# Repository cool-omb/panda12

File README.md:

# panda12

## 概要 Overview

Bluetooth 接続の 12 キーキーボード。

キーマップの変更等がWiFi経由で出来る。

## 使い方 Usage
### キーボード使用時
スライドスイッチで電源を入れ、 `Test_keyboard` にBluetooth接続する。
### キーマップ設定時
設定ボタンを押しながら電源を入れ、 `Preference_keyboard` にWiFi接続する。
ブラウザからキーマップを変更後、 `保存` ボタンをクリックすることで変更が反映される。

※ 有線LANを接続しているデバイスからは、キーマップ変更ページへ自動で遷移しないことがあるので、 `192.168.4.1` へ手動でアクセスしてください。

## 必要要件 Requirement

- KiCad 6.0.10

  - [Kailh socket MX footprint](https://github.com/daprice/keyswitches.pretty)

- [Arduino IDE 2.0.3](https://www.arduino.cc/en/software)
  - [Arduino core for the ESP32 v2.0.4](https://github.com/espressif/arduino-esp32#installation-instructions)
  - [NimBLE-Arduino v1.4.0](https://github.com/h2zero/NimBLE-Arduino)
  - [ESP32-NimBLE-Keyboard v1.4.0](https://github.com/wakwak-koba/ESP32-NimBLE-Keyboard)
  - [arduino-esp8266fs-plugin v0.5.0](https://github.com/esp8266/arduino-esp8266fs-plugin)
  - [Arduino ESP32 filesystem uploader v1.0](https://github.com/me-no-dev/arduino-esp32fs-plugin)
  - [ESP8266_Spiram](https://github.com/Gianbacchio/ESP8266_Spiram)
  - [ESPAsyncWebServer](https://github.com/me-no-dev/ESPAsyncWebServer)
  - [ArduinoJson](https://github.com/bblanchon/ArduinoJson)

## 注意事項 Note
- BLE通信の安定性は上記のライブラリに依存しており、通信するデバイスによっては動作が不安定になることもございます。
- `Blekeyboard.print()` の挙動が不安定で、これを利用しているテキスト出力もまた安定的に動作しません。

## 参考 Reference

- [CaptivePortalExample](https://github.com/elliotmade/ESP32-Captive-Portal-Example/blob/test/src/main.cpp)

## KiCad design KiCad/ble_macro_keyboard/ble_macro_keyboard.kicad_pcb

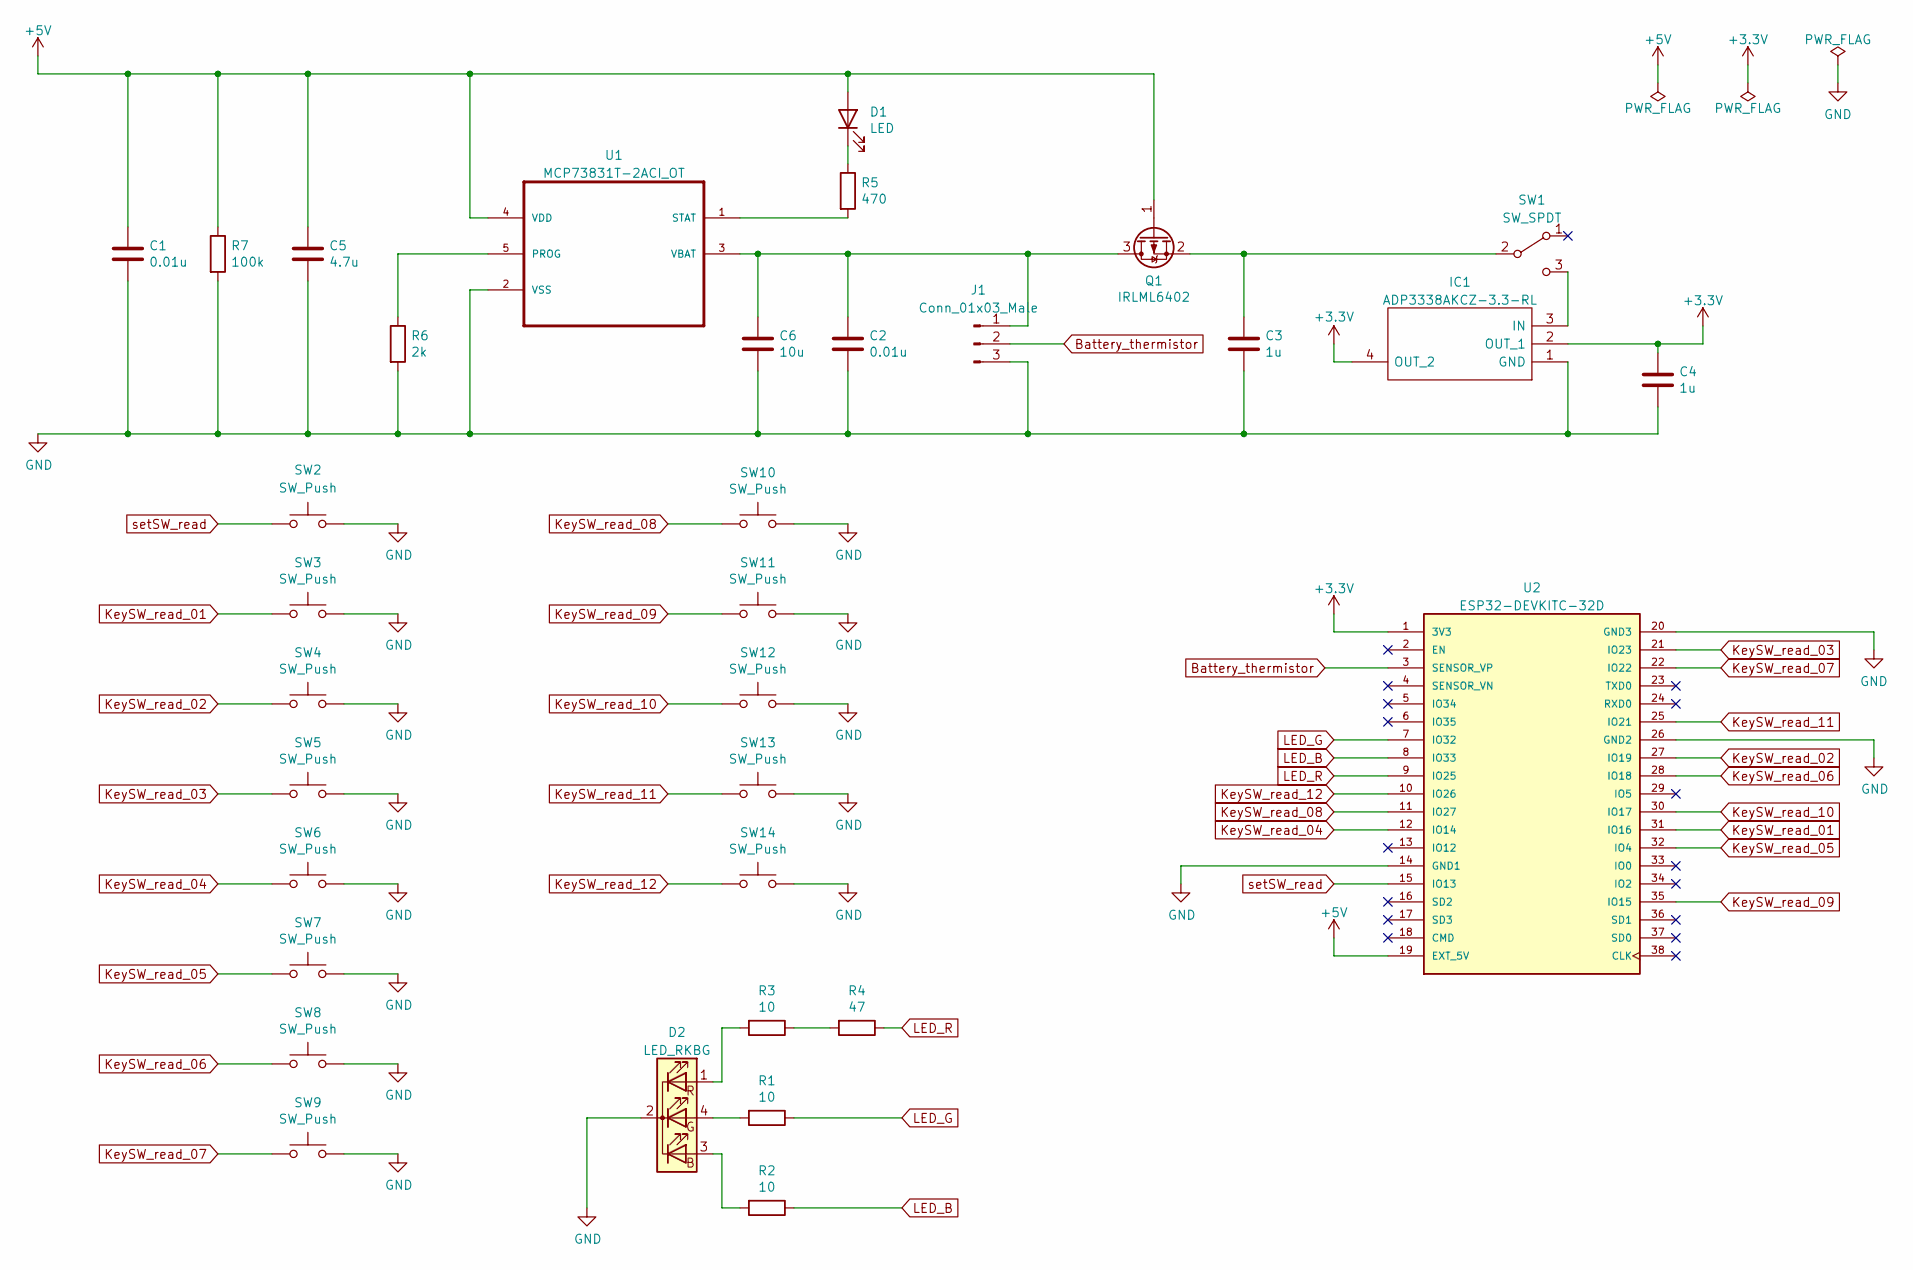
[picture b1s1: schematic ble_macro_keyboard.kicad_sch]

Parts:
C1, C2: 0.01u; C_0603_1608Metric_Pad1.08x0.95mm_HandSolder
C3, C4: 1u; C_0603_1608Metric_Pad1.08x0.95mm_HandSolder
C5: 4.7u; CP_Radial_D5.0mm_P2.00mm
C6: 10u; CP_Radial_D5.0mm_P2.00mm
D1: LED; LED_D3.0mm
D2: LED_RKBG; LED_D5.0mm-4_RGB
IC1: ADP3338AKCZ-3.3-RL; SOT230P700X180-4N; Mouser Part Number 584-ADP3338AKCZ3.3R
J1: Conn_01x03_Male; JST_SHL_SM03B-SHLS-TF_1x03-1MP_P1.00mm_Horizontal
Q1: IRLML6402; SOT-23
R1, R2, R3: 10; R_0603_1608Metric_Pad1.05x0.95mm_HandSolder
R4: 47; R_0603_1608Metric_Pad1.05x0.95mm_HandSolder
R5: 470; R_0603_1608Metric_Pad1.05x0.95mm_HandSolder
R6: 2k; R_0603_1608Metric_Pad1.05x0.95mm_HandSolder
R7: 100k; R_0603_1608Metric_Pad1.05x0.95mm_HandSolder
SW1: SW_SPDT; SW_Slide_SPDT_MSK-12C02
SW2: SW_Push; SW_Push_Dual_x2_TS-4401
SW3, SW4, SW5, SW6, SW7, SW8, SW9, SW10, SW11, SW12, SW13, SW14: SW_Push; Kailh_socket_MX
U1: MCP73831T-2ACI_OT; SOT95P280X145-5N
U2: ESP32-DEVKITC-32D; MODULE_ESP32-DEVKITC-32D; PARTREV 4

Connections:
+3.3V: C4.1, IC1.2 (OUT_1), IC1.4 (OUT_2), U2.1 (3V3)
+5V: C1.1, C5.1, D1.2 (A), Q1.1 (G), R7.1, U1.4 (VDD), U2.19 (EXT_5V)
Battery_thermistor: J1.2, U2.3 (SENSOR_VP)
GND: C1.2, C2.2, C3.2, C4.2, C5.2, C6.2, D2.2 (K), IC1.1 (GND), J1.3, R6.2, R7.2, SW2.2, SW3.2, SW4.2, SW5.2, SW6.2, SW7.2, SW8.2, SW9.2, SW10.2, SW11.2, SW12.2, SW13.2, SW14.2, U1.2 (VSS), U2.14 (GND1), U2.20 (GND3), U2.26 (GND2)
KeySW_read_01: SW3.1, U2.31 (IO16)
KeySW_read_02: SW4.1, U2.27 (IO19)
KeySW_read_03: SW5.1, U2.21 (IO23)
KeySW_read_04: SW6.1, U2.12 (IO14)
KeySW_read_05: SW7.1, U2.32 (IO4)
KeySW_read_06: SW8.1, U2.28 (IO18)
KeySW_read_07: SW9.1, U2.22 (IO22)
KeySW_read_08: SW10.1, U2.11 (IO27)
KeySW_read_09: SW11.1, U2.35 (IO15)
KeySW_read_10: SW12.1, U2.30 (IO17)
KeySW_read_11: SW13.1, U2.25 (IO21)
KeySW_read_12: SW14.1, U2.10 (IO26)
LED_B: R2.1, U2.8 (IO33)
LED_G: R1.1, U2.7 (IO32)
LED_R: R4.1, U2.9 (IO25)
unnamed: C2.1, C6.1, J1.1, Q1.3 (D), U1.3 (VBAT)
unnamed: C3.1, Q1.2 (S), SW1.2 (B)
unnamed: D1.1 (K), R5.1
unnamed: D2.1 (RA), R3.2
unnamed: D2.3 (BA), R2.2
unnamed: D2.4 (GA), R1.2
unnamed: IC1.3 (IN), SW1.3 (C)
unnamed: R3.1, R4.2
unnamed: R5.2, U1.1 (STAT)
unnamed: R6.1, U1.5 (PROG)
setSW_read: SW2.1, U2.15 (IO13)

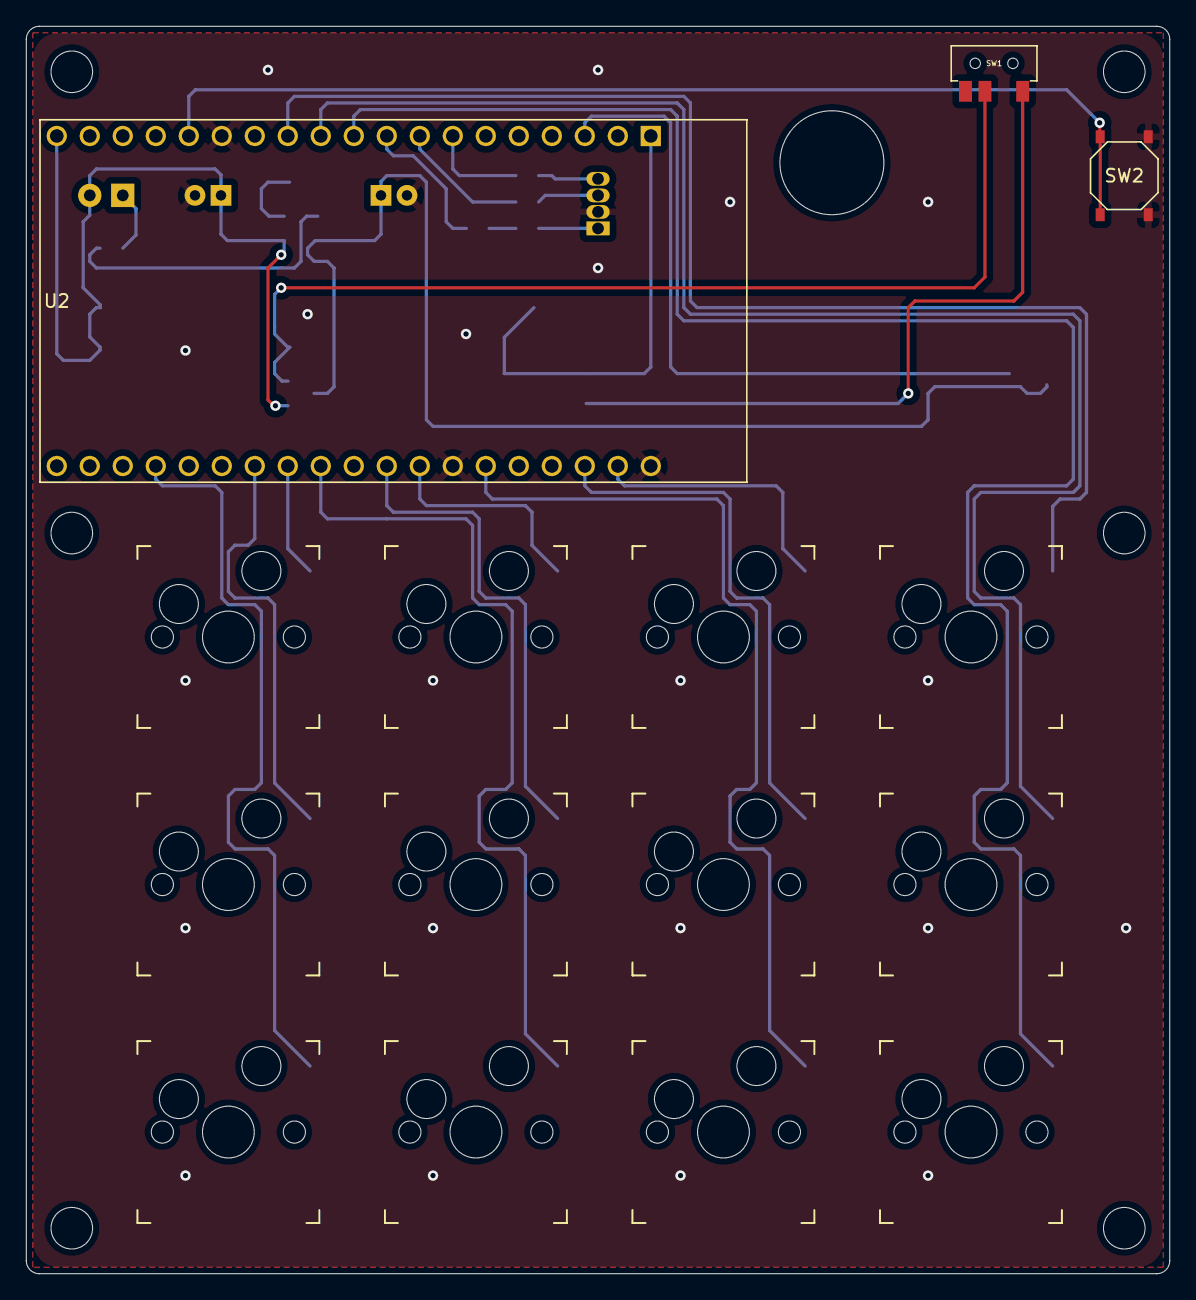
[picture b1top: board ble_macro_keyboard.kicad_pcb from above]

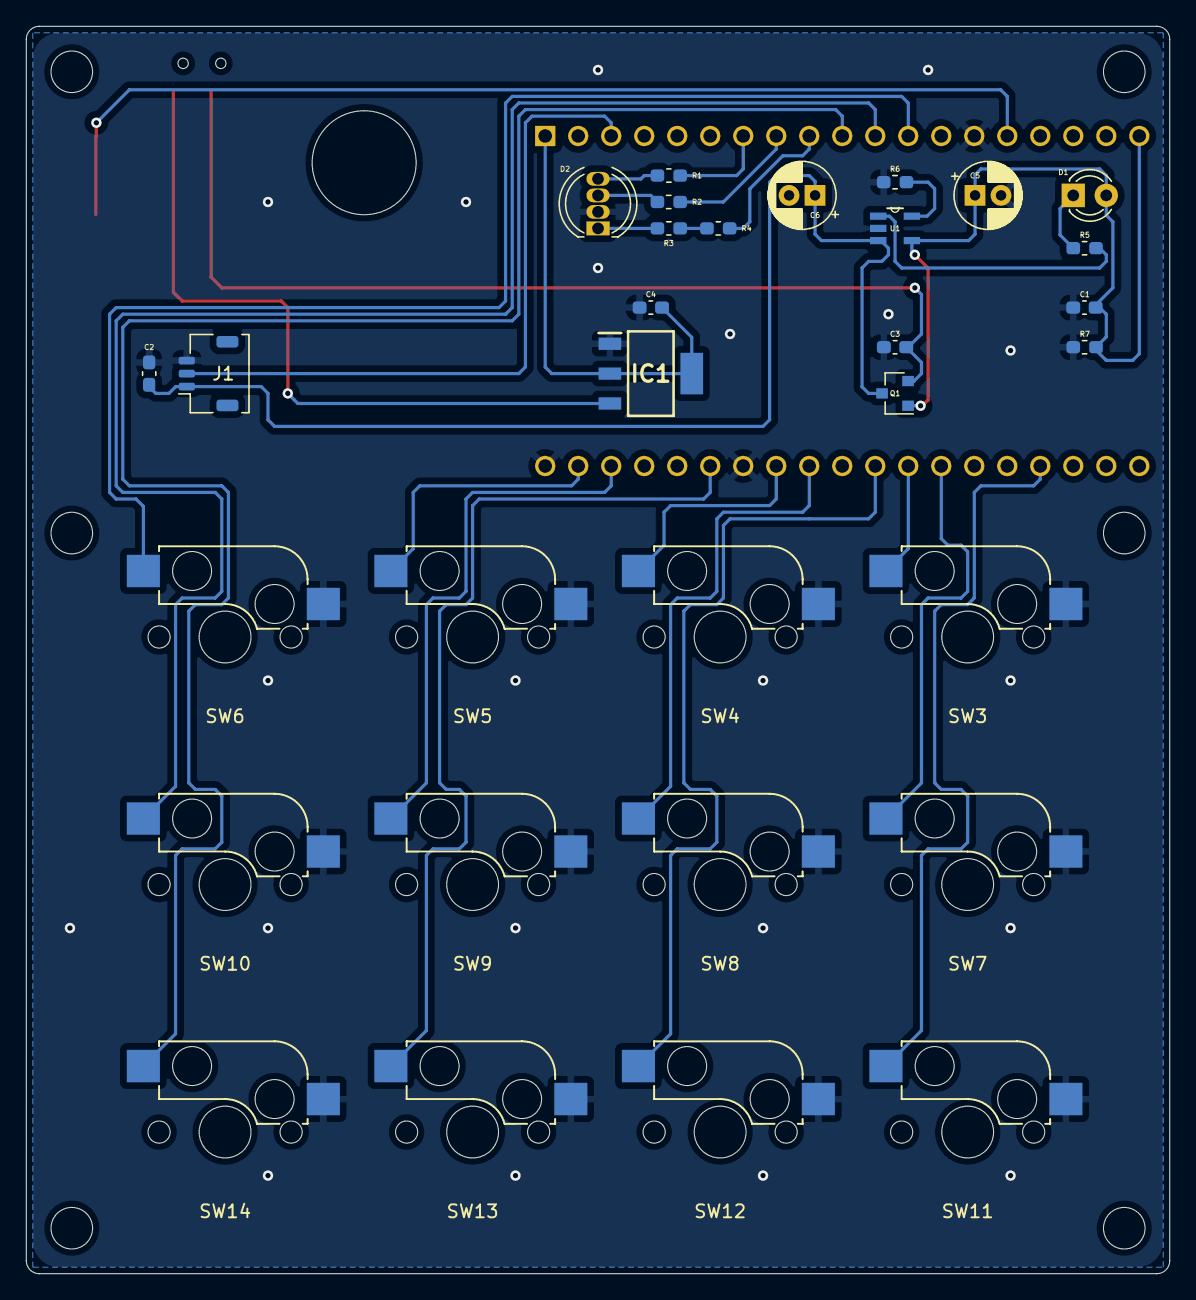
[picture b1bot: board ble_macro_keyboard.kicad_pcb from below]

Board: 2 copper layers, 88.0 x 96.0 mm, 34 parts (19 on the bottom side), 30 nets.

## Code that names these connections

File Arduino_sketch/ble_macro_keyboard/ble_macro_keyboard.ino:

#include <Arduino.h>
#include <AsyncTCP.h>
#include "ESPAsyncWebServer.h"
#include "DNSServer.h"
#include <SPIFFS.h>
#include "ArduinoJson.h"
#include <FS.h>
#include <BleKeyboard.h>

using namespace std;

#define LED_R_PIN 25
#define LED_G_PIN 32
#define LED_B_PIN 33
#define LEDC_BASE_FREQ 12800
#define LEDC_RESOLUTION 8
#define LEDC_CHANNEL_R 0
#define LEDC_CHANNEL_G 1
#define LEDC_CHANNEL_B 2

#define PREFERENCE_SW_PIN 13
#define DEFAULT_DEVICE_NAME "Test_Keyboard"
#define DEFAULT_DEVICE_MANUFACTURER "Panda12_manufacturer"

bool isConfig = false;
const vector<int> SW_PINS{16, 19, 23, 14, 4, 18, 22, 27, 15, 17, 21, 26};

const char *SSID = "Preference_Keyboard";

int LAYER_LENGTH = -1;
int OUTPUT_LENGTH = -1;
int INPUT_LENGTH = -1;
int INTERVAL_MS = 100;
int IS_LED_ON = 0;
int LED_R_BRIGHTNESS = 0;
int LED_G_BRIGHTNESS = 0;
int LED_B_BRIGHTNESS = 0;

AsyncWebServer server(80);
DNSServer dnsServer;

BleKeyboard bleKeyboard(DEFAULT_DEVICE_NAME, DEFAULT_DEVICE_MANUFACTURER, 100);
DynamicJsonDocument preferenceDocument(65536);

void handleUpload(AsyncWebServerRequest *request, String filename, size_t index, uint8_t *data, size_t len, bool final)
{
  return 1;
}

void handleBody(AsyncWebServerRequest *request, uint8_t *data, size_t len, size_t index, size_t total)
{
  if (!index)
  {
    request->_tempFile = SPIFFS.open("/keymap.json", "w");
  }
  request->_tempFile.write(data, len);
  if (index + len == total)
  {
    request->_tempFile.close();
    request->send(200, "text/plain", "Write keymap.json success.");
  }
}

void webServerSetup()
{
  server.serveStatic("/", SPIFFS, "/").setDefaultFile("index.html");
  server.on(
      "/post",
      HTTP_POST,
      [](AsyncWebServerRequest *request)
      {
        request->send(200, "text/plain", "keymap.json posted.");
      },
      handleUpload,
      handleBody);

  server.onNotFound([](AsyncWebServerRequest *request)
                    {
    String redirectUrl = "http://";
    redirectUrl += WiFi.softAPIP().toString();
    redirectUrl += "/";
    request->redirect(redirectUrl); });

  server.begin();
}

void setupLed()
{
  if (IS_LED_ON)
  {
    ledcSetup(LEDC_CHANNEL_R, LEDC_BASE_FREQ, LEDC_RESOLUTION);
    ledcAttachPin(LED_R_PIN, LEDC_CHANNEL_R);
    ledcWrite(LEDC_CHANNEL_R, LED_R_BRIGHTNESS);
    ledcSetup(LEDC_CHANNEL_G, LEDC_BASE_FREQ, LEDC_RESOLUTION);
    ledcAttachPin(LED_G_PIN, LEDC_CHANNEL_G);
    ledcWrite(LEDC_CHANNEL_G, LED_G_BRIGHTNESS);
    ledcSetup(LEDC_CHANNEL_B, LEDC_BASE_FREQ, LEDC_RESOLUTION);
    ledcAttachPin(LED_B_PIN, LEDC_CHANNEL_B);
    ledcWrite(LEDC_CHANNEL_B, LED_B_BRIGHTNESS);
  }
}

void setupPinMode()
{
  pinMode(PREFERENCE_SW_PIN, INPUT_PULLUP);
  for (int pin : SW_PINS)
  {
    pinMode(pin, INPUT_PULLUP);
  }
}

void setupPreferenceMode()
{
  WiFi.softAP(SSID);
  dnsServer.start(53, "*", WiFi.softAPIP());
  webServerSetup();
}

void setupKeyboardMode()
{
  File file = SPIFFS.open("/keymap.json", "r");
  DeserializationError error = deserializeJson(preferenceDocument, file);
  if (error)
  {
    return 0;
  }
  JsonObject root = preferenceDocument.as<JsonObject>();

  file.close();

  LAYER_LENGTH = preferenceDocument["length"]["layer"].as<int>();
  OUTPUT_LENGTH = preferenceDocument["length"]["output"].as<int>();
  INPUT_LENGTH = preferenceDocument["length"]["input"].as<int>();
  INTERVAL_MS = preferenceDocument["preference"]["interval"].as<int>();
  IS_LED_ON = preferenceDocument["preference"]["ledOn"].as<int>();
  LED_R_BRIGHTNESS = preferenceDocument["preference"]["ledRed"].as<int>();
  LED_G_BRIGHTNESS = preferenceDocument["preference"]["ledGreen"].as<int>();
  LED_B_BRIGHTNESS = preferenceDocument["preference"]["ledBlue"].as<int>();

  setupLed();

  delay(20);
  bleKeyboard.begin();
  delay(100);
}

unsigned int readAllPushedBit()
{
  unsigned int pushed = 0;
  for (int i = 0; i < (int)SW_PINS.size(); ++i)
  {
    if (digitalRead(SW_PINS[i]) == LOW)
    {
      pushed |= (1 << i);
    }
  }
  return pushed;
}

int getKeyNumber(int layerIndex, int outputIndex, int inputIndex)
{
  return preferenceDocument["assign"][layerIndex][outputIndex][inputIndex]["num"].as<int>();
}

String getKeyText(int layerIndex, int outputIndex, int inputIndex)
{
  return preferenceDocument["assign"][layerIndex][outputIndex][inputIndex]["text"].as<String>();
}

void loopKeyboard()
{
  // static variable defind.
  static unsigned int swPushedBit = 0;
  static int layerIndex = 0;

  // measures for chattering.
  if (swPushedBit != readAllPushedBit())
  {
    delay(10);
    if (bleKeyboard.isConnected())
    {
      unsigned int currentSwPushedBit = readAllPushedBit();
      unsigned int xorSwPushedBit = currentSwPushedBit ^ swPushedBit;

      int currentLayerIndex = 0;
      for (int i = 0; i < INPUT_LENGTH; ++i)
      {
        if (currentSwPushedBit & (1 << i))
        {
          if (getKeyNumber(0, 0, i) >= 256)
          {
            currentLayerIndex += getKeyNumber(0, 0, i) - 256;
          }
        }
      }
      if (layerIndex != currentLayerIndex)
      {
        bleKeyboard.releaseAll();
        for (int i = 0; i < INPUT_LENGTH; ++i)
        {
          if (currentSwPushedBit & (1 << i))
          {
            int keyNumber = getKeyNumber(currentLayerIndex, 0, i);
            if (keyNumber < 0)
            {
              bleKeyboard.print(getKeyText(currentLayerIndex, 0, i));
            }
            else if (keyNumber < 256)
            {
              bleKeyboard.press(keyNumber);
            }
          }
        }
        layerIndex = currentLayerIndex;
      }
      else
      {
        for (int i = 0; i < (int)SW_PINS.size(); ++i)
        {
          if (xorSwPushedBit & (1 << i))
          {
            int keyNumber = getKeyNumber(currentLayerIndex, 0, i);
            if (currentSwPushedBit & (1 << i))
            {
              if (keyNumber < 0)
              {
                bleKeyboard.print(getKeyText(currentLayerIndex, 0, i));
              }
              else if (keyNumber < 256)
              {
                bleKeyboard.press(keyNumber);
              }
            }
            else
            {
              if (0 <= keyNumber && keyNumber < 256)
              {
                bleKeyboard.release(keyNumber);
              }
            }
          }
        }
      }
      swPushedBit = currentSwPushedBit;
    }
  }
  delay(INTERVAL_MS);
}

void setup()
{
  setupLed();

  SPIFFS.begin();

  setupPinMode();
  if (digitalRead(PREFERENCE_SW_PIN) == LOW)
  {
    isConfig = true;
    setupPreferenceMode();
  }
  else
  {
    setupKeyboardMode();
  }
}

void loop()
{
  if (isConfig)
  {
    dnsServer.processNextRequest();
  }
  else
  {
    loopKeyboard();
  }
}

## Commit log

2021-06-18 add requirement
2021-06-18 add requirement fixed.
2022-06-14 プレゼン向けキー配置
2022-07-10 replace KiCADv6 and new version circuit diagram.
2022-07-10 library replace and connect symbol to footprint.
2022-07-11 add keyswitches.pretty
2022-07-12 keyswitch add to 12.
2022-07-22 ライブラリを相対パスへ変更
2022-07-22 コネクタを除き、シンボルとフットプリントの紐づけ完了
2022-07-22 JST SHコネクタ 3pin のフットプリント作成
2022-07-22 git submodule削除
2022-07-24 基板図配線のためにマイコンのピン入れ替え
2022-07-24 リファレンス指定子を昇順に変更
2022-07-24 シルクスクリーンのリファレンス指定子の印字位置を内側に変更
2022-07-24 [fix] Vsysラベルを3.3vへ修正
2022-07-25 [update] GND以外パターン接続
2022-07-25 [add] ライブラリ及び回路図にNPTH_8mmを追加
2022-07-25 [fix] Ble_keyboardフットプリントライブラリのSWがGNDに接続するように解決
2022-07-25 [fix] Ble_keyboardライブラリのシルクスクリーンとパッドが干渉するライブラリを修正
2022-07-25 [add] 底板の図面出力
2022-07-25 [add] キースイッチプレートの図面出力
2022-07-25 [fix] ハンダマスクの最小幅を0に設定
2022-07-25 [fix] キースイッチプレートの角をフィレット
2022-07-25 [fix] 底板および基板外形の角をフィレット
2022-07-25 [add] 基盤製造用ファイルの出力
2022-07-25 [fix] Elecrow発注用にgerberファイル名変更
2022-07-25 [fix] User.drawingsレイヤーに底板のアクリルプレート、User.Eco1にキースイッチプレートのアクリルの図面を設定
2022-08-02 ignore KiCAD backups
2022-08-02 KiCAD cache file ignore
2022-08-02 [fix] KiCADのキャッシュを除外
2022-08-05 change NimBLE lib.
2022-08-06 [update] 12鍵マクロキーのピン配置に対応
2022-08-08 [fix] ピン配置の宣言をvectorに変更
2022-08-09 [update] EEPROM 読み書きの検証
2022-08-10 [refactor] 変数名の整理
2022-08-10 [refactor] SETTING_SW を keymaps から分離
2022-08-10 [add] キーマップのレイヤー追加
2022-08-10 [fix] vscode exclude
2022-08-10 [fix] Builtin LED delete.
2022-08-10 [add] wifi access point test
2022-08-10 [add] static ip
2022-08-10 [update] device value load rom
2022-08-10 [add] dynamic html create test.
2022-08-10 [add] EEPROM write from HTML.
2022-08-10 [refactor] vector to int array.
2022-08-11 [add] delay_time
2022-08-11 if to switch
2022-08-11 [add] text inputs
2022-08-13 [add] led config add.
2022-08-13 [doc] Readme 必要要件更新
2022-12-26 [add] Pull ISLT65 repo
    Arduino sketch for wifi key preference.
2022-12-27 [add] Add onclick on keysw
    When click key sw, this value put form.
2022-12-27 [add] Change keymap value
    When input and change form value, set changed value to keymap object.
2022-12-27 [update] ESPAsyncWebServer included
    Changed Async from webserver.
2022-12-29 [add] Write json esp32 flash
    POST body to SPIFFS write.
2022-12-29 [add] Preference mode added.
    When push preference sw, Keymap preference mode.
2022-12-29 [add] Read keymap.json
    Load json and get value.
2022-12-29 [add] version1.2
2022-12-29 [update] Added requirement and usage
    Update requirement, usage and note.
2022-12-31 [fix] Changed SSID
    Because SSID is not correct, so it's fixed.
2024-01-03 [doc] Delete debug serial
